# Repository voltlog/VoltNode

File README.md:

# VoltNode™
VoltNode™ is a SA818 based UHF/VHF node designed to be compatible with the open source [SVXLink project](https://github.com/sm0svx/svxlink "SVXLink project"). The PCB was designed to fit over the OrangePiZero and the schematic and GPIO choice is based on the original work of the [ROLink community](http://www.439100.ro/ "ROLink community"), with the goal of having this hardware compatible with ready made OS images create by the ROLink community.

More info about this project in [Voltlog #385](https://youtu.be/EprSIw-5l6w).

Checkout assembly.pdf above for a drawing with component position and designators. This should help when you are assembling the PCB.

Someone designed a [3D printable case](https://www.thingiverse.com/thing:6345499) for the VoltNode. 

Known issues in revA: The mic negative input on the orangepizero is left floating which could lead to some input noise being amplified. A fix is indicated in the schematic.

revB: Addressed the issue by addig capacitor to MIC1N.

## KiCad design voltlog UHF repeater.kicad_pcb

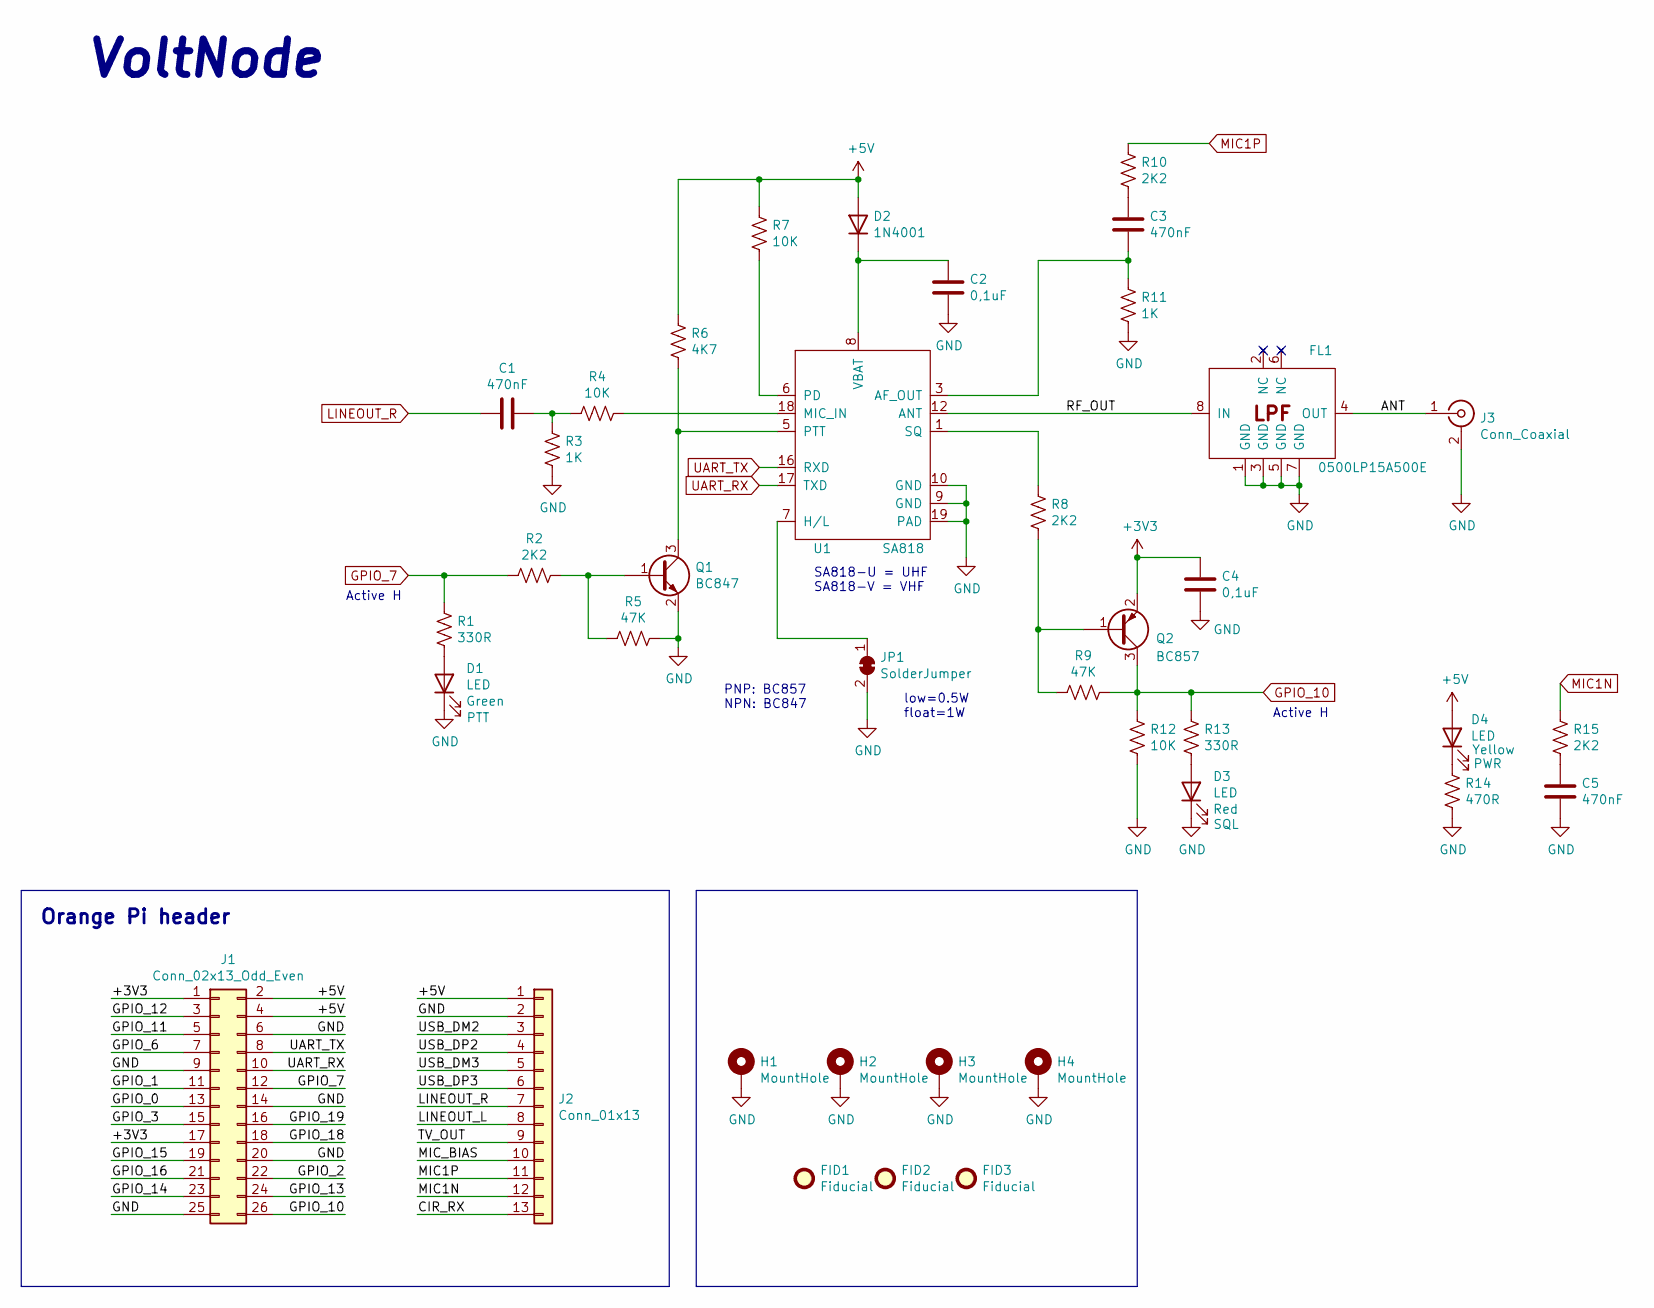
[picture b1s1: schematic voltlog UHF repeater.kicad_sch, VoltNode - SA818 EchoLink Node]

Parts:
C1, C3, C5: 470nF; C_0603_1608Metric
C2, C4: 0,1uF; C_0603_1608Metric
D1: LED; LED_0603_1608Metric; JLCPCB Part # C72043
D2: 1N4001; D_SMA
D3: LED; LED_0603_1608Metric; JLCPCB Part # C2286
D4: LED; LED_0603_1608Metric; JLCPCB Part # C72038
FID1, FID2, FID3: Fiducial; Fiducial_0.5mm_Mask1mm
FL1: 0500LP15A500E; 0500LP15A500
H1, H2, H3, H4: MountHole; MountingHole_3.2mm_M3_ISO14580_Pad
J1: Conn_02x13_Odd_Even; PinHeader_2x13_P2.54mm_Vertical
J2: Conn_01x13; PinHeader_1x13_P2.54mm_Vertical
J3: Conn_Coaxial; SMA_Amphenol_132134_Vertical; JLCPCB Part # C914559
JP1: SolderJumper; SolderJumper-2_P1.3mm_Open_TrianglePad1.0x1.5mm
Q1: BC847; SOT-23
Q2: BC857; SOT-23
R1, R13: 330R; R_0603_1608Metric
R2, R8, R10, R15: 2K2; R_0603_1608Metric
R3, R11: 1K; R_0603_1608Metric
R4, R7, R12: 10K; R_0603_1608Metric
R5, R9: 47K; R_0603_1608Metric
R6: 4K7; R_0603_1608Metric
R14: 470R; R_0603_1608Metric
U1: SA818

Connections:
+3V3: C4.1, J1.1, J1.17, Q2.2 (E)
+5V: D2.2 (A), D4.2 (A), J1.2, J1.4, J2.1, R6.1, R7.1
/ANT: FL1.4 (OUT), J3.1 (In)
/CIR_RX: J2.13
/GPIO_0: J1.13
/GPIO_1: J1.11
/GPIO_2: J1.22
/GPIO_3: J1.15
/GPIO_6: J1.7
/GPIO_11: J1.5
/GPIO_12: J1.3
/GPIO_13: J1.24
/GPIO_14: J1.23
/GPIO_15: J1.19
/GPIO_16: J1.21
/GPIO_18: J1.18
/GPIO_19: J1.16
/LINEOUT_L: J2.8
/MIC_BIAS: J2.10
/RF_OUT: FL1.8 (IN), U1.12 (ANT)
/TV_OUT: J2.9
/USB_DM2: J2.3
/USB_DM3: J2.5
/USB_DP2: J2.4
/USB_DP3: J2.6
GND: C2.2, C4.2, C5.2, D1.1 (K), D3.1 (K), FL1.1 (GND), FL1.3 (GND), FL1.5 (GND), FL1.7 (GND), H1.1, H2.1, H3.1, H4.1, J1.6, J1.9, J1.14, J1.20, J1.25, J2.2, J3.2 (Ext), JP1.2 (B), Q1.2 (E), R3.2, R5.1, R11.2, R12.2, R14.2, U1.9 (GND), U1.10 (GND), U1.19 (PAD)
GPIO_7: J1.12, R1.1, R2.2
GPIO_10: J1.26, Q2.3 (C), R9.2, R12.1, R13.1
LINEOUT_R: C1.2, J2.7
MIC1N: J2.12, R15.1
MIC1P: J2.11, R10.1
unnamed: C1.1, R3.1, R4.2
unnamed: C3.1, R10.2
unnamed: C5.1, R15.2
unnamed: D1.2 (A), R1.2
unnamed: C2.1, D2.1 (K), U1.8 (VBAT)
unnamed: D3.2 (A), R13.2
unnamed: D4.1 (K), R14.1
unnamed: JP1.1 (A), U1.7 (H/L)
unnamed: Q1.1 (B), R2.1, R5.2
unnamed: Q1.3 (C), R6.2, U1.5 (PTT)
unnamed: Q2.1 (B), R8.2, R9.1
unnamed: C3.2, R11.1, U1.3 (AF_OUT)
unnamed: R4.1, U1.18 (MIC_IN)
unnamed: R7.2, U1.6 (PD)
unnamed: R8.1, U1.1 (SQ)
UART_RX: J1.10, U1.17 (TXD)
UART_TX: J1.8, U1.16 (RXD)

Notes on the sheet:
Orange Pi header
SA818-U = UHF SA818-V = VHF
Active H
low=0.5W float=1W
VoltNode
PNP: BC857 NPN: BC847

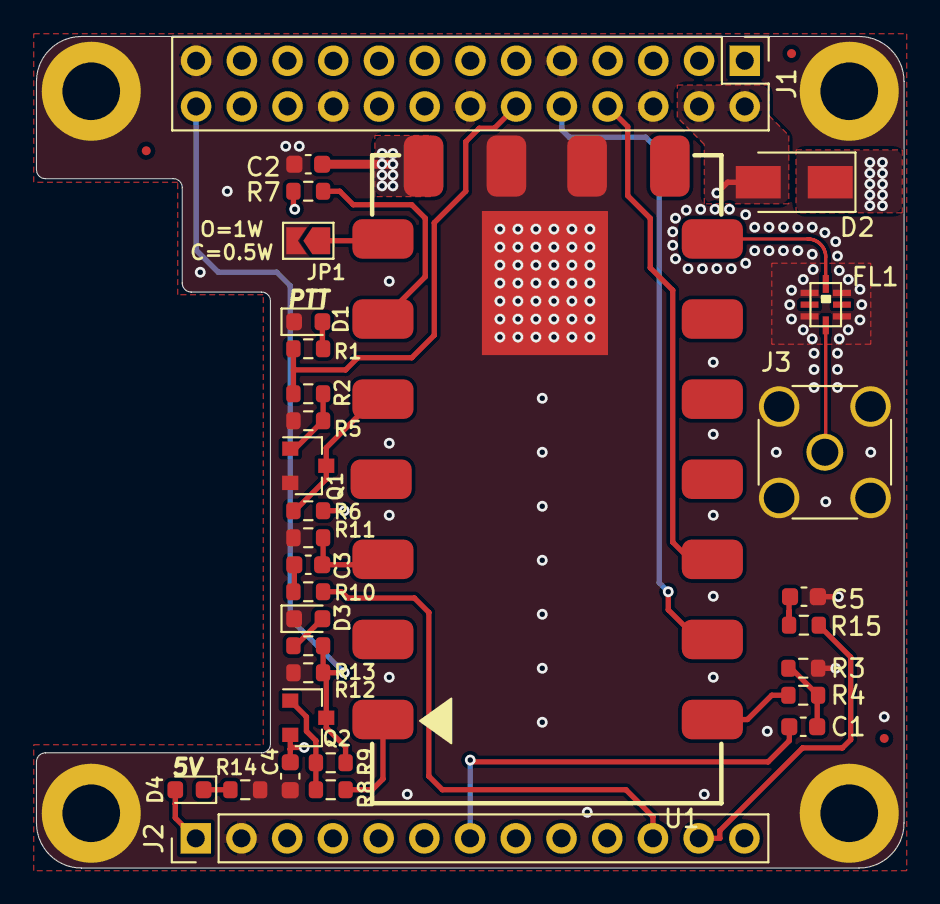
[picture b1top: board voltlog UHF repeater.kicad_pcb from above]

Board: 4 copper layers, 48.2 x 46.2 mm, 39 parts (0 on the bottom side), 27 nets.

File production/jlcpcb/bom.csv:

Designator,Footprint,Quantity,Value,LCSC Part #
"C1, C3, C5",0603,3,470nF,
"C2, C4",0603,2,"0,1uF",
D1,0603,1,LED,C72043
D2,D_SMA,1,1N4001,
D3,0603,1,LED,C2286
D4,0603,1,LED,C72038
FL1,0500LP15A500,1,0500LP15A500E,
J3,SMA_Amphenol_132134_Vertical,1,Conn_Coaxial,C914559
Q1,SOT-23,1,BC847,
Q2,SOT-23,1,BC857,
"R1, R13",0603,2,330R,
"R10, R15, R2, R8",0603,4,2K2,
"R11, R3",0603,2,1K,
"R12, R4, R7",0603,3,10K,
R14,0603,1,470R,
"R5, R9",0603,2,47K,
R6,0603,1,4K7,
U1,SA818,1,SA818,

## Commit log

2021-10-26 Added component placement drawing
2023-10-03 Added pulldown for MIC1N. Added part no for JLCPCB and production files for JLCPCB.
2023-10-04 Fixed errors caused by orangepi outline present in Margin layer
2023-10-04 Removed logo from schemantic. Removed H1-H4, Fid1-Fid3, J1, J2 and JP1 from BOM and POS file.
2023-10-04 Cleanup in bom and position file.
2023-12-04 Added link to 3D printable enclosure
